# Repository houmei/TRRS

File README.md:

# TRRS 3.5mm 4pole plug converter (KiCad5)

Schematic

PCB

部品表  

J1-J3 [３．５ｍｍ４極ミニジャック　基板取付用　ＭＪ－４ＰＰ－９](https://akizukidenshi.com/catalog/g/gC-06070/)  
J4 [ピンヘッダ　１×４　（４Ｐ）　（１０個入）](https://akizukidenshi.com/catalog/g/gC-03950/) など ※オプション  
J5 [基板用RCAジャック 黄 RJ-2410](https://akizukidenshi.com/catalog/g/gC-06508/)  
または [基板用RCAジャック 白 MJ-523](https://akizukidenshi.com/catalog/g/gC-16497/)  
または [基板用RCAジャック 黒 RJ-2410](https://akizukidenshi.com/catalog/g/gC-16500/)  
J6 [３．５ｍｍ小型ステレオミニジャック　基板取付用](https://akizukidenshi.com/catalog/g/gC-02460/)  
J7 [３．５ｍｍステレオミニジャック　基板取付用　ＭＪ－８４３５](https://akizukidenshi.com/catalog/g/gC-09060/)  
※J6,J7はどちらかひとつでよい　　

## 説明

[TRRS 4極3.5mmジャックの変換基板](http://blog.livedoor.jp/hardyboy/archives/10396121.html)  
<!-- [DIN8RJ45V01L04 デジタルRGBをVGA RJ45コネクタに変換](http://blog.livedoor.jp/hardyboy/archives/10203256.html "まごころせいじつ堂")   -->
<!-- [SORD m5用ROM/RAMカートリッジ基板](https://keisanki.booth.pm/items/3939000 "booth")  -->

## 履歴
V01L01 初版  

## TRRSV01L01GB - Gerber
JLCPCBなどにそのまま出図可能です。

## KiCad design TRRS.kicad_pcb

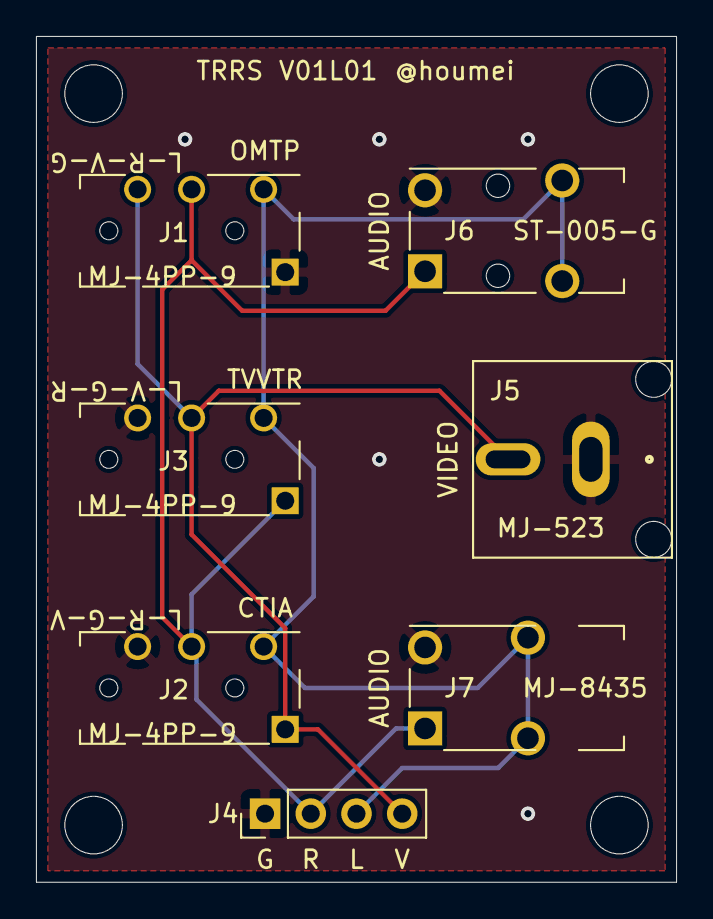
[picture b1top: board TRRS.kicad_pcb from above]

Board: 2 copper layers, 35.6 x 47.0 mm, 7 parts (0 on the bottom side), 4 nets.

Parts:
J1, J2, J3: AudioJack4; Jack_3.5mm_MJ-4PP-9
J4: Conn_01x04_Male; PinHeader_1x04_P2.54mm_Vertical
J5: Conn_Coaxial; MJ-523
J6: AudioJack3; Jack_3.5mm_ST-005-G_WH
J7: AudioJack3; Jack_3.5mm_MRUSHIN_MJ-8435

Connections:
GND: J1.S, J2.R2, J3.R2, J4.1, J5.2, J6.S, J7.S
L: J1.T, J2.T, J3.T, J4.3, J6.T, J7.T
R: J1.R1, J2.R1, J3.S, J4.2, J6.R, J7.R
V: J1.R2, J2.S, J3.R1, J4.4, J5.1

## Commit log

2023-07-09 V01L01
